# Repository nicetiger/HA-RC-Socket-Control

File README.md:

# Home Assistant RC-Socket Control

This repository contains the documentation and code for building a

It uses the following:
-  Wemos D1 mini pro (ESP8266)
-  433 MHz radio - transmitter and receiver module
-  BMP180 Barometric air pressure and temperature sensor
-  [ESPHome](https://esphome.io)
-  [RC-Switch](https://github.com/sui77/rc-switch)

## PCB

The board was manufactured here:
https://aisler.net/p/YNNSZLZG

## Flashing a NodeMCU

1. Provide a `secrets.yaml` file using `secrets.yaml.example` as a guideline
2. Clone this repository, `cd` into its sub directory `ESPHome`
3. Connect a NodeMCU to your computer using a Micro USB cable
4. Flash the NodeMCU using the following command or one of [ESPHome](https://esphome.io)'s own Getting Started guides:

```bash
docker run --rm -v ${PWD}:/config -it esphome/esphome run sensor.yaml
```

## The wiring and soldering part

schema and layout:

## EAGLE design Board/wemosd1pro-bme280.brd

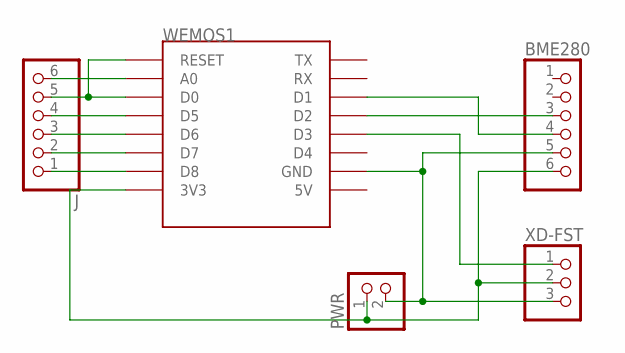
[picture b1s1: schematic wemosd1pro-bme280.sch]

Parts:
BME280: PINHD-1X6; 1X06
J: PINHD-1X6; 1X06
PWR: PINHD-1X2; 1X02
WEMOS1: WEMOS-D1-MINI
XD-FST: PINHD-1X3; 1X03

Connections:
unnamed: BME280.6, PWR.1, WEMOS1.3V3, XD-FST.2
unnamed: BME280.5, PWR.2, WEMOS1.GND, XD-FST.3
unnamed: J.5, WEMOS1.D0, WEMOS1.RESET
unnamed: BME280.4, WEMOS1.D1
unnamed: BME280.3, WEMOS1.D2
unnamed: WEMOS1.D3, XD-FST.1
unnamed: J.1, WEMOS1.D8
unnamed: J.2, WEMOS1.D7
unnamed: J.3, WEMOS1.D6
unnamed: J.4, WEMOS1.D5
unnamed: J.6, WEMOS1.A0

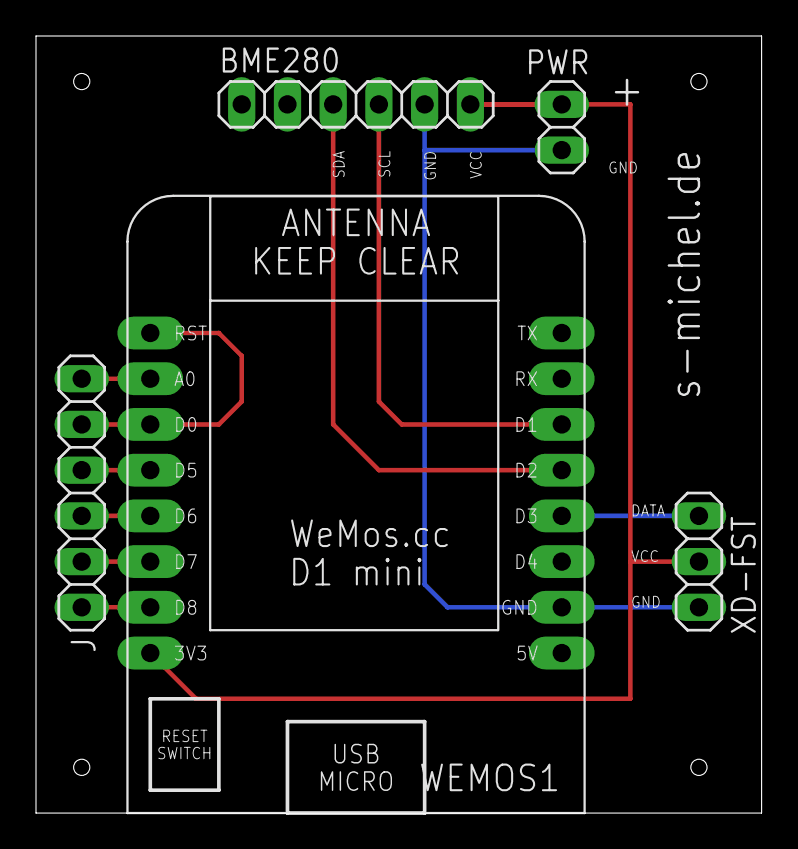
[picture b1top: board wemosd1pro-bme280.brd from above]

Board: 2 copper layers, 40.3 x 43.2 mm, 5 parts (0 on the bottom side), 11 nets.

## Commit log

2021-11-27 initial version
